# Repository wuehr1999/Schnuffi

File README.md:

# Schnuffi
A small linefollowing and micromouse robot.

## Sensors
* 9 ITR1201 light sensors
* 5 VL53L0X tof sensors
* HAL Encoder input for each motor

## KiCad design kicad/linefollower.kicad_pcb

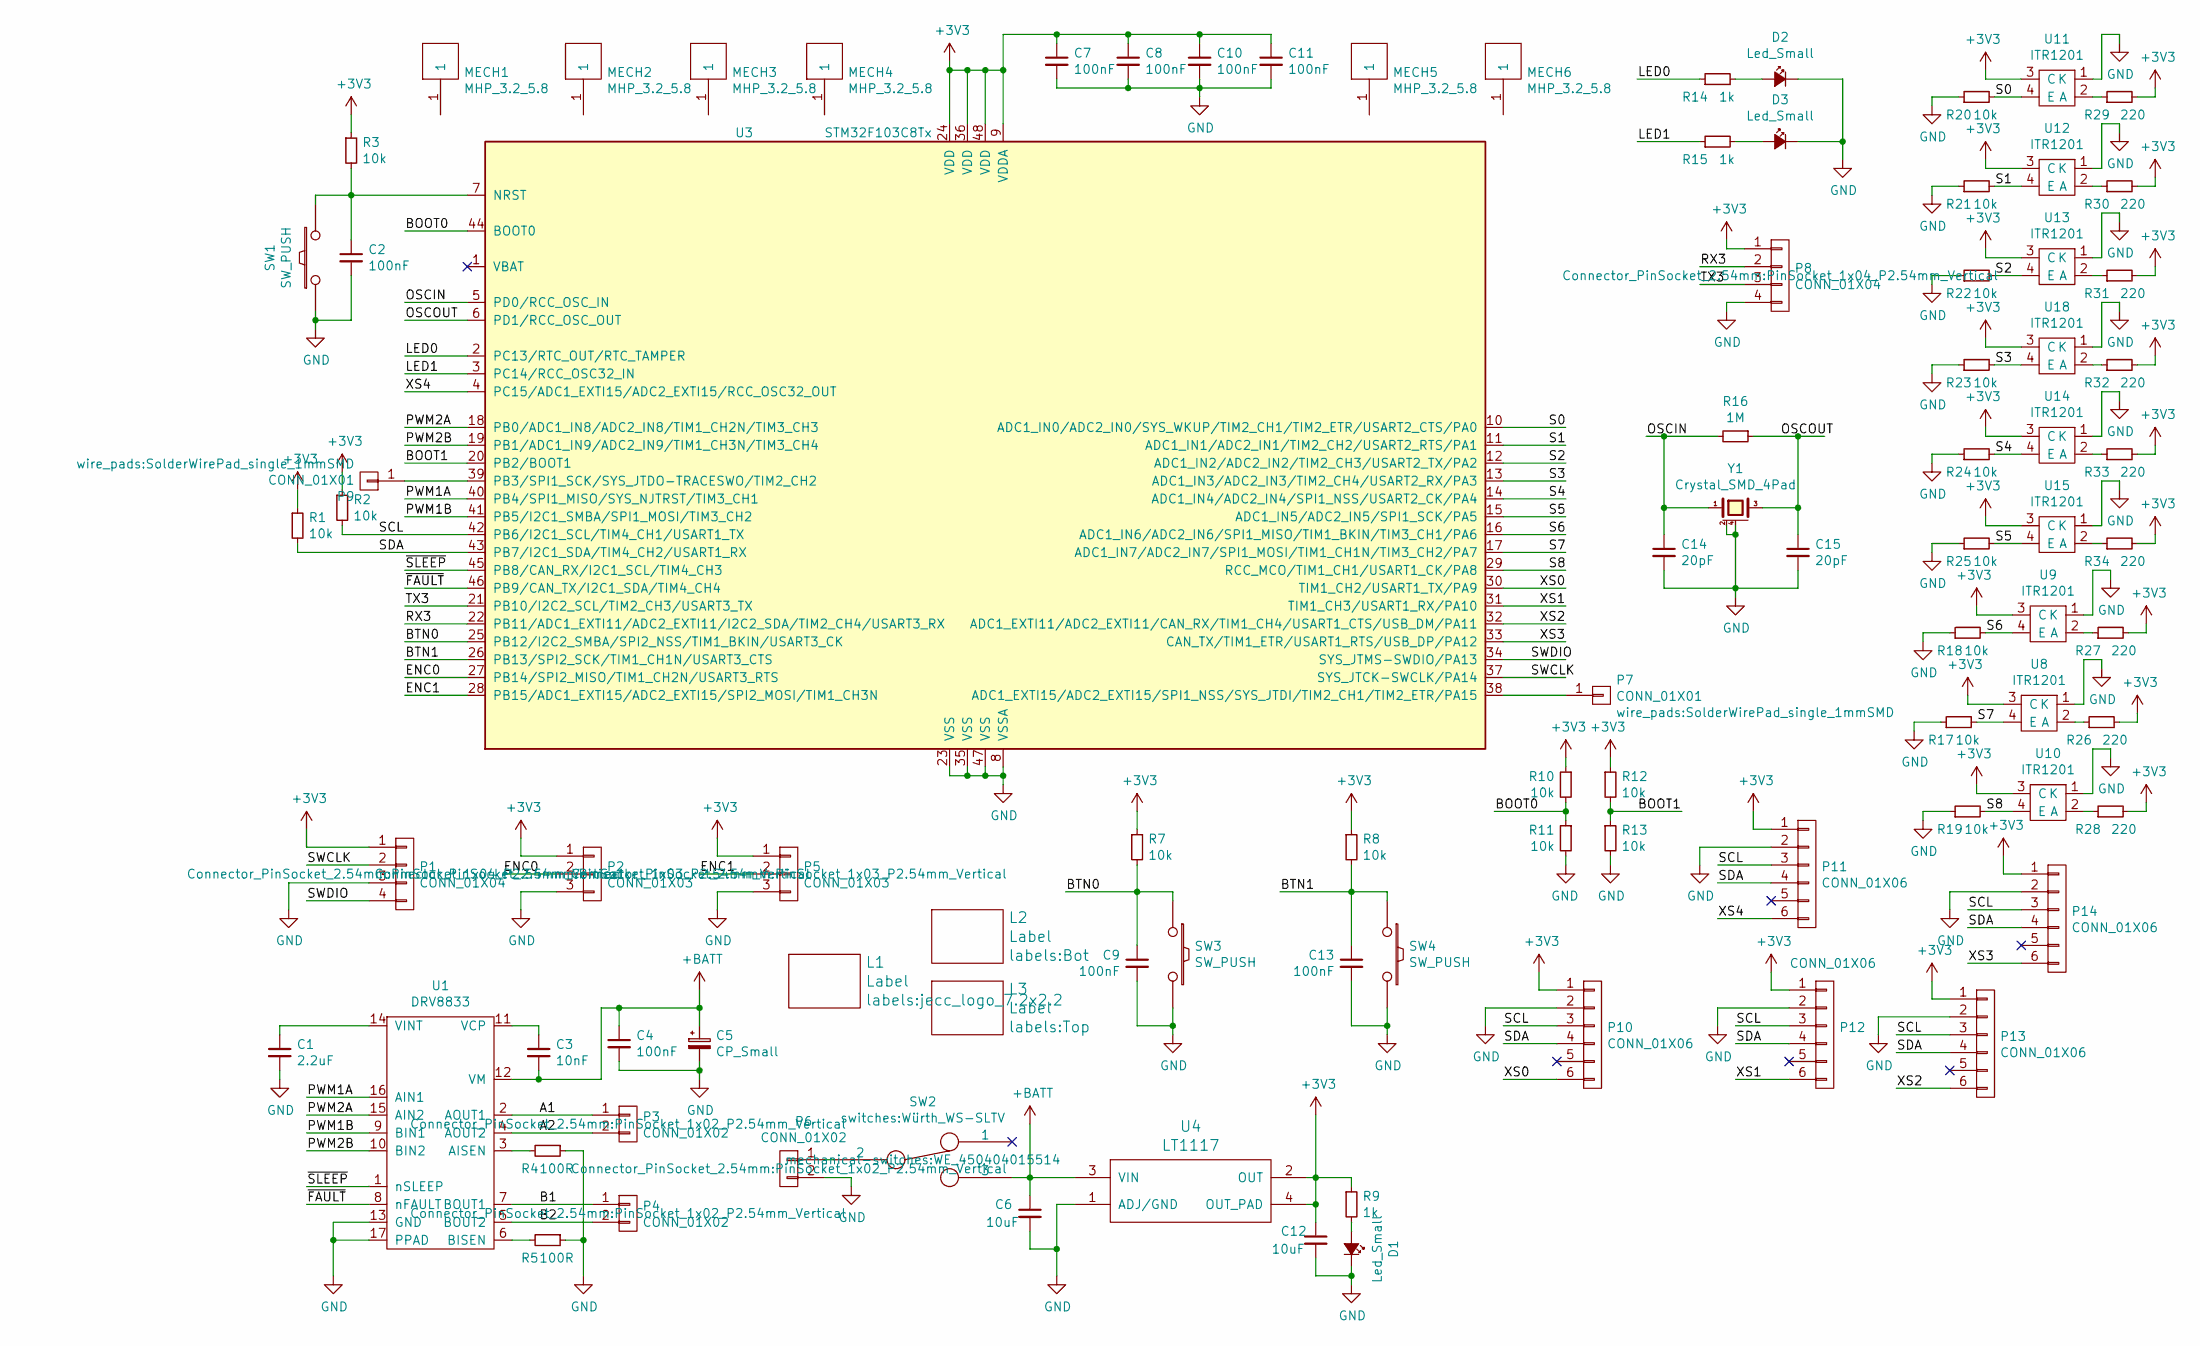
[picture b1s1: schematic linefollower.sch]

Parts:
C1: 2.2uF; C_0603
C2, C4, C7, C8, C9, C10, C11, C13: 100nF; C_0603
C3: 10nF; C_0603
C5: CP_Small; TantalC_SizeX_EIA-7343
C6, C12: 10uF; C_1206
C14, C15: 20pF; C_0603
D1, D2, D3: Led_Small; LED_0603
L1: Label; jecc_logo_7.2x2.2
L2: Label; Bot
L3: Label; Top
MECH1, MECH2, MECH3, MECH4, MECH5, MECH6: MHP_3.2_5.8
P1, P8: CONN_01X04; PinSocket_1x04_P2.54mm_Vertical
P2, P5: CONN_01X03; PinSocket_1x03_P2.54mm_Vertical
P3, P4, P6: CONN_01X02; PinSocket_1x02_P2.54mm_Vertical
P7, P9: CONN_01X01; SolderWirePad_single_1mmSMD
P10, P11, P12, P13, P14: CONN_01X06; PinHeader_1x06_P2.54mm_Vertical
R1, R2, R3, R7, R8, R10, R11, R12, R13, R17, R18, R19, R20, R21, R22, R23, R24, R25: 10k; R_0603
R4, R5: 100R; R_0805
R9, R14, R15: 1k; R_0603
R16: 1M; R_0603
R26, R27, R28, R29, R30, R31, R32, R33, R34: 220; R_0603
SW1, SW3, SW4: SW_PUSH; smd_push
SW2: switches:Würth_WS-SLTV; WE_450404015514
U1: DRV8833; TSSOP-16-1EP_4.4x5mm_Pitch0.65mm
U3: STM32F103C8Tx; LQFP-48_7x7mm_Pitch0.5mm
U4: LT1117; SOT-223
U8, U9, U10, U11, U12, U13, U14, U15, U18: ITR1201
Y1: Crystal_SMD_4Pad; Crystal_SMD_0603_4Pads

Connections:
+3V3: C7.1, C8.1, C10.1, C11.1, C12.1, P1.1, P2.1, P5.1, P8.1, P10.1, P11.1, P12.1, P13.1, P14.1, R1.1, R2.1, R3.1, R7.1, R8.1, R9.1, R10.1, R12.1, R26.2, R27.2, R28.2, R29.2, R30.2, R31.2, R32.2, R33.2, R34.2, U3.9 (VDDA), U3.24 (VDD), U3.36 (VDD), U3.48 (VDD), U4.2 (OUT), U4.4 (OUT_PAD), U8.3 (C), U9.3 (C), U10.3 (C), U11.3 (C), U12.3 (C), U13.3 (C), U14.3 (C), U15.3 (C), U18.3 (C)
+BATT: C3.2, C4.1, C5.1, C6.1, SW2.3, U1.12 (VM), U4.3 (VIN)
/A1: P3.1, U1.2 (AOUT1)
/A2: P3.2, U1.4 (AOUT2)
/B1: P4.1, U1.7 (BOUT1)
/B2: P4.2, U1.5 (BOUT2)
/BOOT0: R10.2, R11.1, U3.44 (BOOT0)
/BOOT1: R12.2, R13.1, U3.20 (PB2/BOOT1)
/BTN0: C9.1, R7.2, SW3.1, U3.25 (PB12/I2C2_SMBA/SPI2_NSS/TIM1_BKIN/USART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)
/BTN1: C13.1, R8.2, SW4.1, U3.26 (PB13/SPI2_SCK/TIM1_CH1N/USART3_CTS)
/ENC0: P2.2, U3.27 (PB14/SPI2_MISO/TIM1_CH2N/USART3_RTS)
/ENC1: P5.2, U3.28 (PB15/ADC1_EXTI15/ADC2_EXTI15/SPI2_MOSI/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)
/LED0: R14.1, U3.2 (PC13/RTC_OUT/RTC_TAMPER)
/LED1: R15.1, U3.3 (PC14/RCC_OSC32_IN)
/OSCIN: C14.1, R16.2, U3.5 (PD0/RCC_OSC_IN), Y1.1
/OSCOUT: C15.1, R16.1, U3.6 (PD1/RCC_OSC_OUT), Y1.3
/PWM1A: U1.16 (AIN1), U3.40 (PB4/SPI1_MISO/SYS_NJTRST/TIM3_CH1)
/PWM1B: U1.9 (BIN1), U3.41 (PB5/I2C1_SMBA/SPI1_MOSI/TIM3_CH2)
/PWM2A: U1.15 (AIN2), U3.18 (PB0/ADC1_IN8/ADC2_IN8/TIM1_CH2N/TIM3_CH3)
/PWM2B: U1.10 (BIN2), U3.19 (PB1/ADC1_IN9/ADC2_IN9/TIM1_CH3N/TIM3_CH4)
/RX3: P8.2, U3.22 (PB11/ADC1_EXTI11/ADC2_EXTI11/I2C2_SDA/T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)
/S0: R20.2, U3.10 (ADC1_IN0/ADC2_IN0/SYS_WKUP/TIM2_CH1/TIM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), U11.4 (E)
/S1: R21.2, U3.11 (ADC1_IN1/ADC2_IN1/TIM2_CH2/USART2_RTS/P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), U12.4 (E)
/S2: R22.2, U3.12 (ADC1_IN2/ADC2_IN2/TIM2_CH3/USART2_TX/PA2), U13.4 (E)
/S3: R23.2, U3.13 (ADC1_IN3/ADC2_IN3/TIM2_CH4/USART2_RX/PA3), U18.4 (E)
/S4: R24.2, U3.14 (ADC1_IN4/ADC2_IN4/SPI1_NSS/USART2_CK/PA4), U14.4 (E)
/S5: R25.2, U3.15 (ADC1_IN5/ADC2_IN5/SPI1_SCK/PA5), U15.4 (E)
/S6: R18.2, U3.16 (ADC1_IN6/ADC2_IN6/SPI1_MISO/TIM1_BKIN/T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), U9.4 (E)
/S7: R17.2, U3.17 (ADC1_IN7/ADC2_IN7/SPI1_MOSI/TIM1_CH1N/T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), U8.4 (E)
/S8: R19.2, U3.29 (RCC_MCO/TIM1_CH1/USART1_CK/PA8), U10.4 (E)
/SCL: P10.3, P11.3, P12.3, P13.3, P14.3, R2.2, U3.42 (PB6/I2C1_SCL/TIM4_CH1/USART1_TX)
/SDA: P10.4, P11.4, P12.4, P13.4, P14.4, R1.2, U3.43 (PB7/I2C1_SDA/TIM4_CH2/USART1_RX)
/SWCLK: P1.2, U3.37 (SYS_JTCK-SWCLK/PA14)
/SWDIO: P1.4, U3.34 (SYS_JTMS-SWDIO/PA13)
/TX3: P8.3, U3.21 (PB10/I2C2_SCL/TIM2_CH3/USART3_TX)
/XS0: P10.6, U3.30 (TIM1_CH2/USART1_TX/PA9)
/XS1: P12.6, U3.31 (TIM1_CH3/USART1_RX/PA10)
/XS2: P13.6, U3.32 (ADC1_EXTI11/ADC2_EXTI11/CAN_RX/TIM1_CH4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)
/XS3: P14.6, U3.33 (CAN_TX/TIM1_ETR/USART1_RTS/USB_DP/PA12)
/XS4: P11.6, U3.4 (PC15/ADC1_EXTI15/ADC2_EXTI15/RCC_OSC32_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)
/~FAULT: U1.8 (nFAULT), U3.46 (PB9/CAN_TX/I2C1_SDA/TIM4_CH4)
/~SLEEP: U1.1 (nSLEEP), U3.45 (PB8/CAN_RX/I2C1_SCL/TIM4_CH3)
GND: C1.2, C2.2, C4.2, C5.2, C6.2, C7.2, C8.2, C9.2, C10.2, C11.2, C12.2, C13.2, C14.2, C15.2, D1.1 (K), D2.1 (K), D3.1 (K), P1.3, P2.3, P5.3, P6.2, P8.4, P10.2, P11.2, P12.2, P13.2, P14.2, R4.1, R5.1, R11.2, R13.2, R17.1, R18.1, R19.1, R20.1, R21.1, R22.1, R23.1, R24.1, R25.1, SW1.1, SW3.2, SW4.2, U1.13 (GND), U1.17 (PPAD), U3.8 (VSSA), U3.23 (VSS), U3.35 (VSS), U3.47 (VSS), U4.1 (ADJ/GND), U8.1 (K), U9.1 (K), U10.1 (K), U11.1 (K), U12.1 (K), U13.1 (K), U14.1 (K), U15.1 (K), U18.1 (K), Y1.2 (case), Y1.4 (case)
unnamed: C1.1, U1.14 (VINT)
unnamed: C2.1, R3.2, SW1.2, U3.7 (NRST)
unnamed: C3.1, U1.11 (VCP)
unnamed: D1.2 (A), R9.2
unnamed: D2.2 (A), R14.2
unnamed: D3.2 (A), R15.2
unnamed: P6.1, SW2.2
unnamed: P7.1, U3.38 (ADC1_EXTI15/ADC2_EXTI15/SPI1_NSS/SYS_JT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)
unnamed: P9.1, U3.39 (PB3/SPI1_SCK/SYS_JTDO-TRACESWO/TIM2_CH2)
unnamed: R4.2, U1.3 (AISEN)
unnamed: R5.2, U1.6 (BISEN)
unnamed: R26.1, U8.2 (A)
unnamed: R27.1, U9.2 (A)
unnamed: R28.1, U10.2 (A)
unnamed: R29.1, U11.2 (A)
unnamed: R30.1, U12.2 (A)
unnamed: R31.1, U13.2 (A)
unnamed: R32.1, U18.2 (A)
unnamed: R33.1, U14.2 (A)
unnamed: R34.1, U15.2 (A)

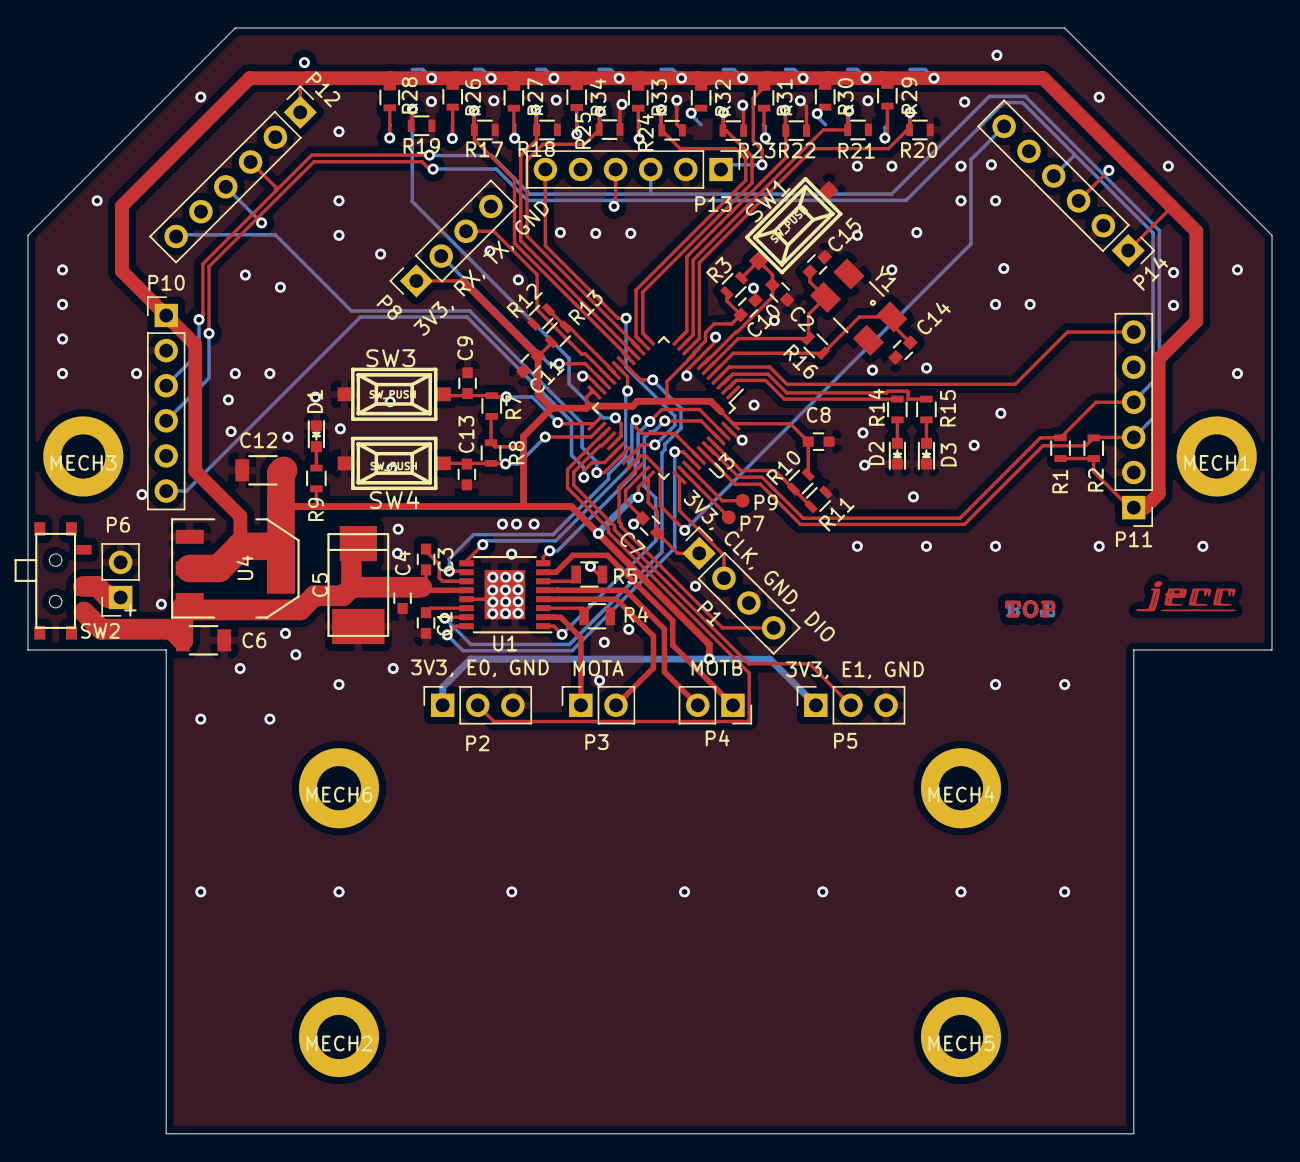
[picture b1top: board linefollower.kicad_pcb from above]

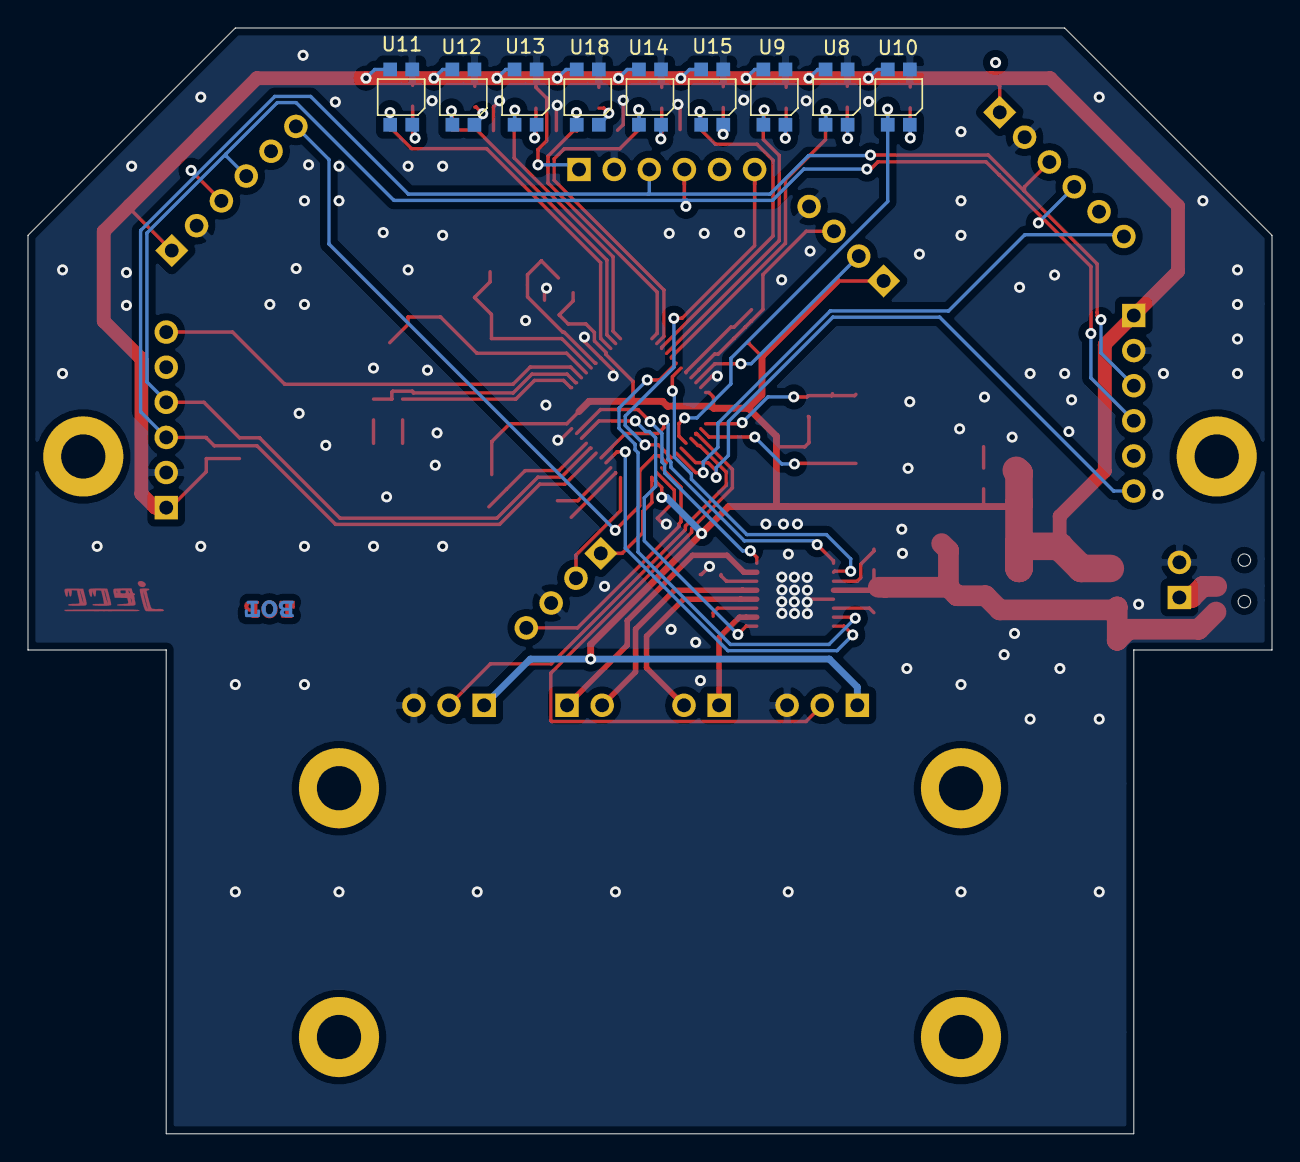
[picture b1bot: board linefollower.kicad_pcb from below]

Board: 2 copper layers, 90.0 x 80.0 mm, 91 parts (9 on the bottom side), 63 nets.

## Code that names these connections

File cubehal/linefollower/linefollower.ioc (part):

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PB13.GPIOParameters=GPIO_Label
Mcu.UserName=STM32F103C8Tx
PB10.Mode=Asynchronous
PC13-TAMPER-RTC.GPIOParameters=GPIO_Label
PB14.GPIO_Label=ENC0
PA12.GPIOParameters=GPIO_Label
PA9.GPIOParameters=GPIO_Label
PA11.GPIOParameters=GPIO_Label
PA3.GPIOParameters=GPIO_Label
PA6.GPIO_Label=S6
PB0.GPIO_Label=PWM2
PB6.GPIO_Label=SCL
PB13.GPIO_Label=BTN1
PB11.Signal=USART3_RX
PB13.Signal=GPIO_Input
PB15.Signal=GPXTI15
PA2.GPIOParameters=GPIO_Label
PC15-OSC32_OUT.GPIO_Label=XS4
RCC.SYSCLKSource=RCC_SYSCLKSOURCE_PLLCLK
PB5.GPIOParameters=GPIO_Label
PD1-OSC_OUT.Signal=RCC_OSC_OUT
PA15.GPIO_Label=TP1
PB4.GPIOParameters=GPIO_Label
PA12.Signal=GPIO_Output
PB6.Signal=GPIO_Output
PA8.GPIOParameters=GPIO_PuPd,GPIO_Label
PA0-WKUP.GPIOParameters=GPIO_Label
PB12.GPIO_Label=BTN0
PB0.GPIOParameters=GPIO_Label
PA1.GPIOParameters=GPIO_Label
PA14.Mode=Serial_Wire
PB1.GPIO_Label=PWM1
PA10.GPIO_Label=XS1
PB3.GPIOParameters=GPIO_Label
PB7.Signal=GPIO_Input
PA8.Signal=GPIO_Input
PB6.GPIOParameters=GPIO_Label,GPIO_ModeDefaultOutputPP
PC14-OSC32_IN.GPIOParameters=GPIO_Label
PB7.GPIO_Label=SDA
Mcu.Package=LQFP48
PB9.Signal=GPIO_Input
PB14.GPIO_PuPd=GPIO_PULLUP
PB1.Signal=S_TIM3_CH4
PA6.Signal=ADCx_IN6
PB15.GPIO_PuPd=GPIO_PULLUP
PA2.GPIO_Label=S2
PB6.GPIO_ModeDefaultOutputPP=GPIO_MODE_OUTPUT_OD
PA10.Signal=GPIO_Output
PA15.Signal=GPIO_Output
PA5.GPIOParameters=GPIO_Label
PB14.GPIOParameters=GPIO_PuPd,GPIO_Label
PB5.GPIO_Label=PWM4
PC14-OSC32_IN.GPIO_Label=LED1
PC15-OSC32_OUT.GPIOParameters=GPIO_Label
PA4.GPIO_Label=S4
PB4.Signal=S_TIM3_CH1
PA3.Signal=ADCx_IN3
PB3.GPIO_Label=TP2
PA6.GPIOParameters=GPIO_Label
PB8.GPIOParameters=GPIO_Label
PD1-OSC_OUT.Mode=HSE-External-Oscillator
PB9.GPIO_Label=nFAULT
PA15.GPIOParameters=GPIO_Label
PA9.GPIO_Label=XS0
PC13-TAMPER-RTC.Signal=GPIO_Output
PA11.GPIO_Label=XS2
PD0-OSC_IN.Signal=RCC_OSC_IN
PC14-OSC32_IN.Signal=GPIO_Output
PA12.GPIO_Label=XS3
PA0-WKUP.GPIO_Label=S0
PA0-WKUP.Signal=ADCx_IN0
PB9.GPIOParameters=GPIO_Label
PA13.Signal=SYS_JTMS-SWDIO
PB8.GPIO_Label=nSLEEP
PA8.GPIO_Label=S8
PB11.Mode=Asynchronous
PB7.GPIOParameters=GPIO_Label
PA9.Signal=GPIO_Output
PC15-OSC32_OUT.Signal=GPIO_Output
PA1.Signal=ADCx_IN1
PD0-OSC_IN.Mode=HSE-External-Oscillator
PB10.Signal=USART3_TX
PB14.Signal=GPXTI14
PA5.Signal=ADCx_IN5
board=custom
PC13-TAMPER-RTC.GPIO_Label=LED0
PB4.GPIO_Label=PWM3
PB15.GPIO_Label=ENC1
PA1.GPIO_Label=S1
PA10.GPIOParameters=GPIO_Label
PA4.GPIOParameters=GPIO_Label
PB15.GPIOParameters=GPIO_PuPd,GPIO_Label
PA13.Mode=Serial_Wire
Mcu.Name=STM32F103C(8-B)Tx
PA2.Signal=ADCx_IN2
PB3.Signal=GPIO_Output
PA4.Signal=ADCx_IN4
RCC.SYSCLKFreq_VALUE=72000000
PB5.Signal=S_TIM3_CH2
PA7.GPIO_Label=S7
PA5.GPIO_Label=S5
PA11.Signal=GPIO_Output
PA14.Signal=SYS_JTCK-SWCLK
PA8.GPIO_PuPd=GPIO_PULLUP
PB8.Signal=GPIO_Output
PB0.Signal=S_TIM3_CH3
PA7.GPIOParameters=GPIO_Label
PB12.GPIOParameters=GPIO_Label
PB12.Signal=GPIO_Input
PA3.GPIO_Label=S3
PB1.GPIOParameters=GPIO_Label
PA7.Signal=ADCx_IN7

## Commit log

2021-05-16 init
